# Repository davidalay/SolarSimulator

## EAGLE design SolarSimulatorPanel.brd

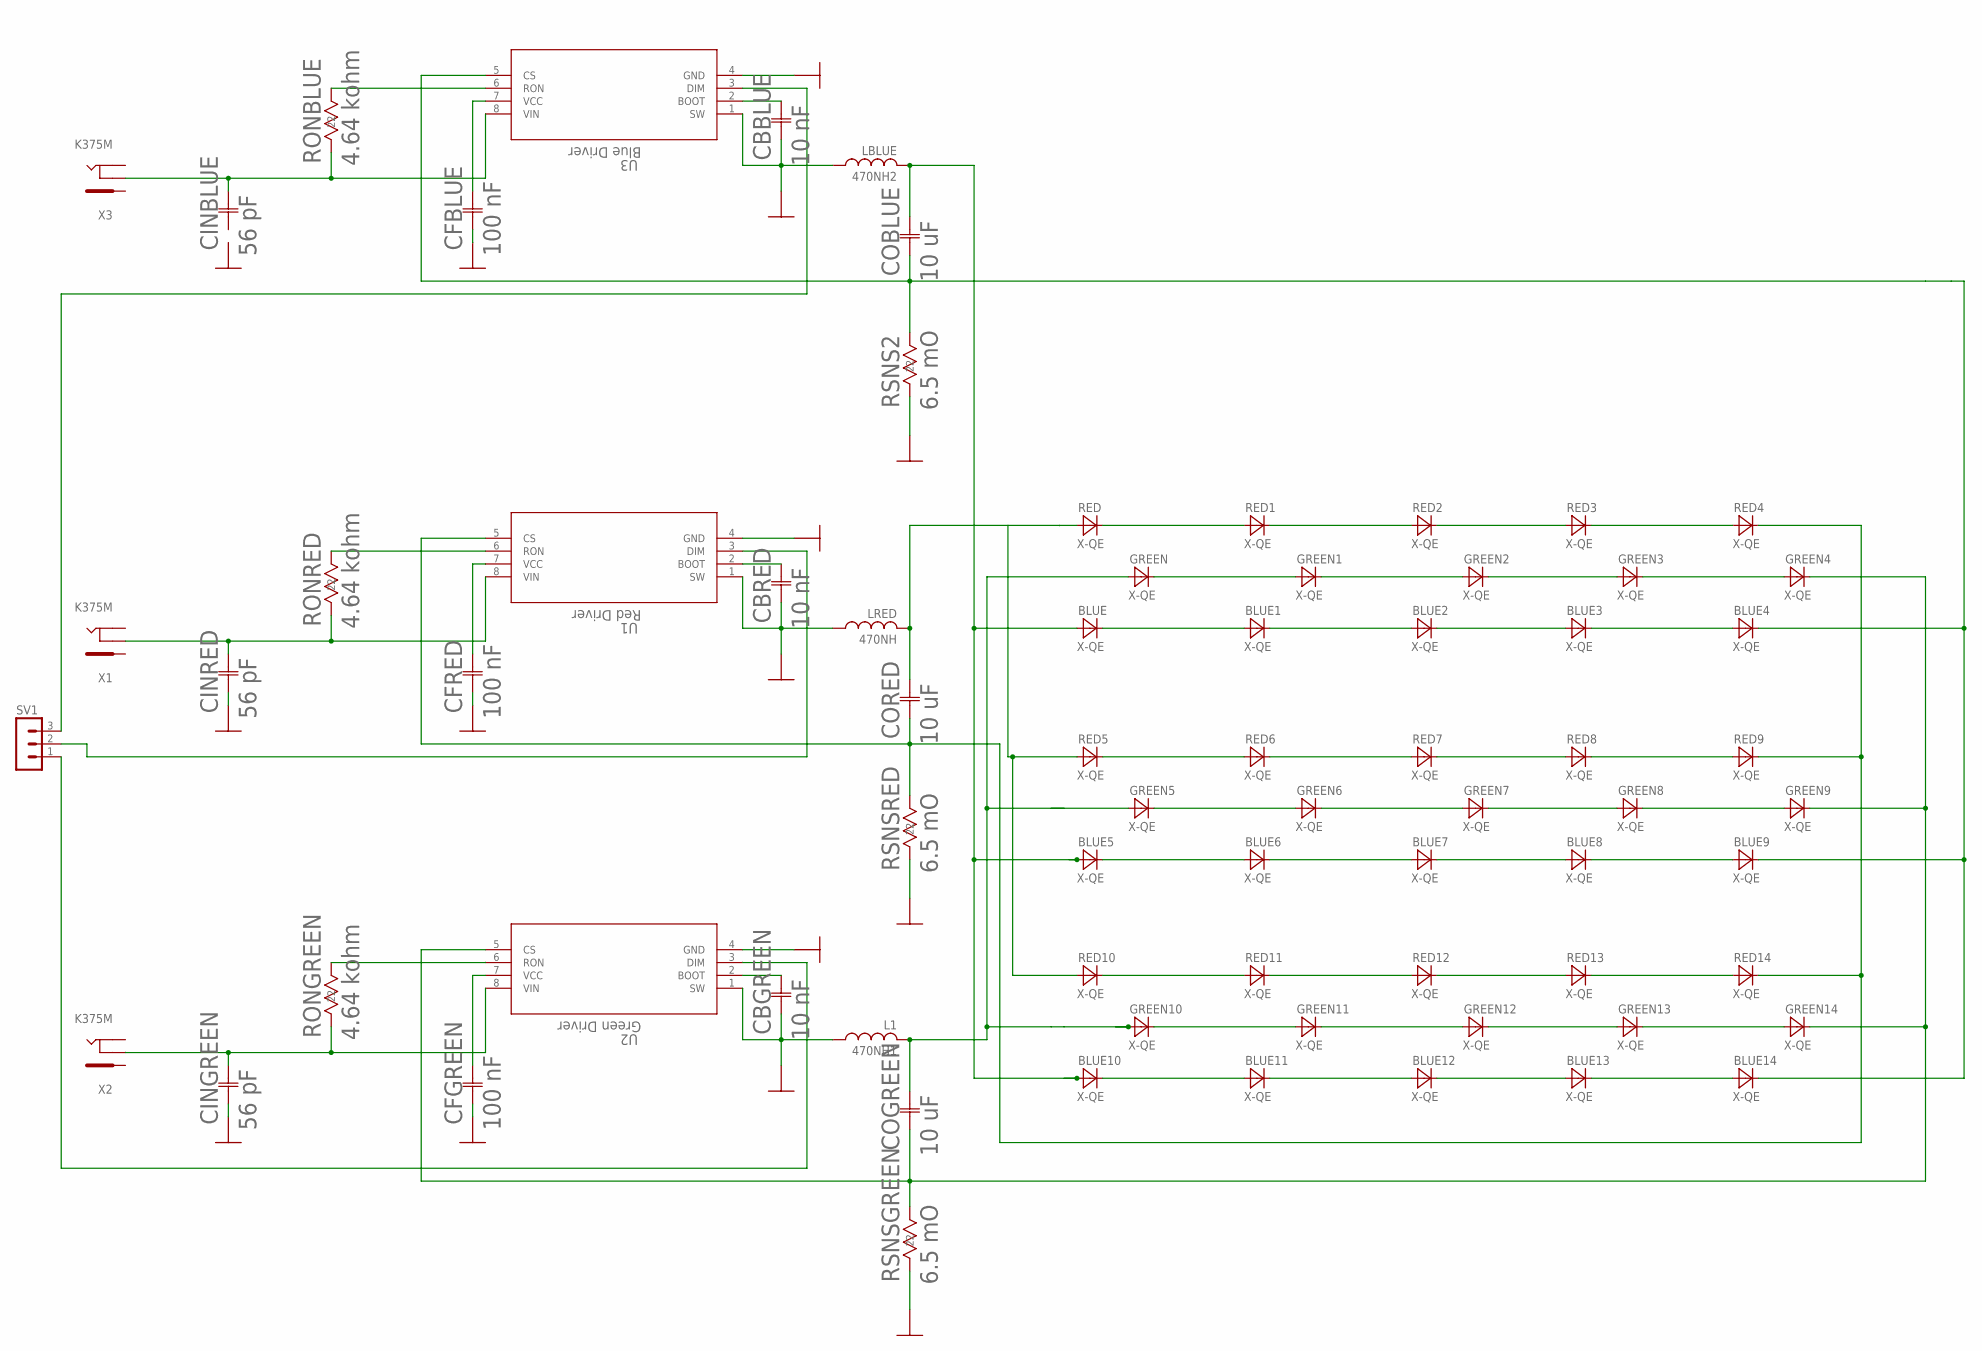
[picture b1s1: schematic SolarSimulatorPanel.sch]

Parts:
470NH: LRED; CAPC2012X135N
470NH1: L1; CAPC2012X135N
470NH2: LBLUE; CAPC2012X135N
BLUE, BLUE1, BLUE2, BLUE3, BLUE4, BLUE5, BLUE6, BLUE7, BLUE8, BLUE9, BLUE10, BLUE11, BLUE12, BLUE13, BLUE14: X-QE
CBBLUE: 10 nF; C1206K
CBGREEN: 10 nF; C1206K
CBRED: 10 nF; C1206K
CFBLUE: 100 nF; C1206
CFGREEN: 100 nF; C1206
CFRED: 100 nF; C1206
CINBLUE: 56 pF; CAP_0603G
CINGREEN: 56 pF; CAP_0603G
CINRED: 56 pF; CAP_0603G
COBLUE: 10 uF; CAP_3225
COGREEN: 10 uF; CAP_3225
CORED: 10 uF; CAP_3225
GREEN, GREEN1, GREEN2, GREEN3, GREEN4, GREEN5, GREEN6, GREEN7, GREEN8, GREEN9, GREEN10, GREEN11, GREEN12, GREEN13, GREEN14: X-QE
RED, RED1, RED2, RED3, RED4, RED5, RED6, RED7, RED8, RED9, RED10, RED11, RED12, RED13, RED14: X-QE
RONBLUE: 4.64 kohm; RC0603N
RONGREEN: 4.64 kohm; RC0603N
RONRED: 4.64 kohm; RC0603N
RSNS2: 6.5 mO; R2512
RSNSGREEN: 6.5 mO; R2512
RSNSRED: 6.5 mO; R2512
SV1: MA03-1
U1: Red Driver; M08A
U2: Green Driver; M08A
U3: Blue Driver; M08A
X1, X2, X3: K375M

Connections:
unnamed: CINRED.2 (22), RONRED.2 (22), U1.8 (VIN), X1.3
unnamed: 470NH.1, CBRED.1 (11), U1.1 (SW)
unnamed: 470NH.2, CORED.2 (22), RED.INPUT (A), RED5.INPUT (A), RED10.INPUT (A)
unnamed: CFRED.2 (22), U1.7 (VCC)
unnamed: RED5.OUTPUT (C), RED6.INPUT (A)
unnamed: RONRED.1 (11), U1.6 (RON)
unnamed: RED6.OUTPUT (C), RED7.INPUT (A)
unnamed: RED7.OUTPUT (C), RED8.INPUT (A)
unnamed: RED8.OUTPUT (C), RED9.INPUT (A)
unnamed: RED10.OUTPUT (C), RED11.INPUT (A)
unnamed: RED11.OUTPUT (C), RED12.INPUT (A)
unnamed: RED12.OUTPUT (C), RED13.INPUT (A)
unnamed: RED13.OUTPUT (C), RED14.INPUT (A)
unnamed: RED.OUTPUT (C), RED1.INPUT (A)
unnamed: RED1.OUTPUT (C), RED2.INPUT (A)
unnamed: RED2.OUTPUT (C), RED3.INPUT (A)
unnamed: RED3.OUTPUT (C), RED4.INPUT (A)
unnamed: 470NH2.1, CBBLUE.1 (11), U3.1 (SW)
unnamed: SV1.2, U1.3 (DIM)
unnamed: CBRED.2 (22), U1.2 (BOOT)
unnamed: 470NH1.1, CBGREEN.1 (11), U2.1 (SW)
unnamed: RONGREEN.1 (11), U2.6 (RON)
unnamed: CINGREEN.2 (22), RONGREEN.2 (22), U2.8 (VIN), X2.3
unnamed: COGREEN.1 (11), GREEN4.OUTPUT (C), GREEN9.OUTPUT (C), GREEN14.OUTPUT (C), RSNSGREEN.1 (11), U2.5 (CS)
unnamed: SV1.1, U2.3 (DIM)
unnamed: CBGREEN.2 (22), U2.2 (BOOT)
unnamed: CFGREEN.2 (22), U2.7 (VCC)
unnamed: GREEN.OUTPUT (C), GREEN1.INPUT (A)
unnamed: GREEN1.OUTPUT (C), GREEN2.INPUT (A)
unnamed: GREEN2.OUTPUT (C), GREEN3.INPUT (A)
unnamed: GREEN3.OUTPUT (C), GREEN4.INPUT (A)
unnamed: GREEN5.OUTPUT (C), GREEN6.INPUT (A)
unnamed: GREEN6.OUTPUT (C), GREEN7.INPUT (A)
unnamed: GREEN7.OUTPUT (C), GREEN8.INPUT (A)
unnamed: GREEN8.OUTPUT (C), GREEN9.INPUT (A)
unnamed: GREEN10.OUTPUT (C), GREEN11.INPUT (A)
unnamed: GREEN11.OUTPUT (C), GREEN12.INPUT (A)
unnamed: GREEN12.OUTPUT (C), GREEN13.INPUT (A)
unnamed: GREEN13.OUTPUT (C), GREEN14.INPUT (A)
unnamed: BLUE.OUTPUT (C), BLUE1.INPUT (A)
unnamed: RONBLUE.1 (11), U3.6 (RON)
unnamed: CINBLUE.2 (22), RONBLUE.2 (22), U3.8 (VIN), X3.3
unnamed: SV1.3, U3.3 (DIM)
unnamed: CBBLUE.2 (22), U3.2 (BOOT)
unnamed: CFBLUE.2 (22), U3.7 (VCC)
unnamed: BLUE1.OUTPUT (C), BLUE2.INPUT (A)
unnamed: BLUE2.OUTPUT (C), BLUE3.INPUT (A)
unnamed: BLUE3.OUTPUT (C), BLUE4.INPUT (A)
unnamed: BLUE5.OUTPUT (C), BLUE6.INPUT (A)
unnamed: BLUE6.OUTPUT (C), BLUE7.INPUT (A)
unnamed: BLUE7.OUTPUT (C), BLUE8.INPUT (A)
unnamed: BLUE8.OUTPUT (C), BLUE9.INPUT (A)
unnamed: BLUE10.OUTPUT (C), BLUE11.INPUT (A)
unnamed: BLUE11.OUTPUT (C), BLUE12.INPUT (A)
unnamed: BLUE12.OUTPUT (C), BLUE13.INPUT (A)
unnamed: BLUE13.OUTPUT (C), BLUE14.INPUT (A)
unnamed: BLUE4.OUTPUT (C), BLUE9.OUTPUT (C), BLUE14.OUTPUT (C), COBLUE.1 (11), RSNS2.1 (11), U3.5 (CS)
unnamed: 470NH2.2, BLUE.INPUT (A), BLUE5.INPUT (A), BLUE10.INPUT (A), COBLUE.2 (22)
unnamed: CORED.1 (11), RED4.OUTPUT (C), RED9.OUTPUT (C), RED14.OUTPUT (C), RSNSRED.1 (11), U1.5 (CS)
unnamed: 470NH1.2, COGREEN.2 (22), GREEN.INPUT (A), GREEN10.INPUT (A)

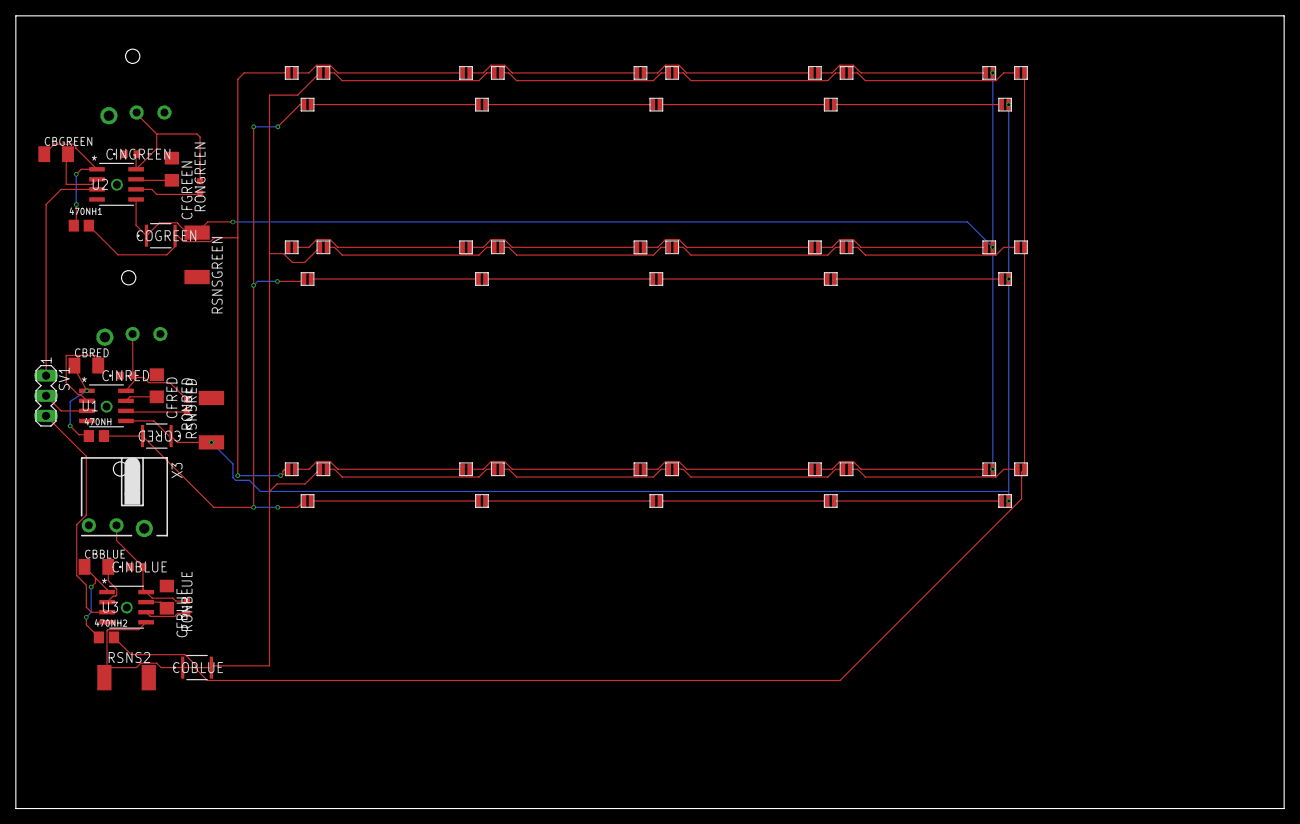
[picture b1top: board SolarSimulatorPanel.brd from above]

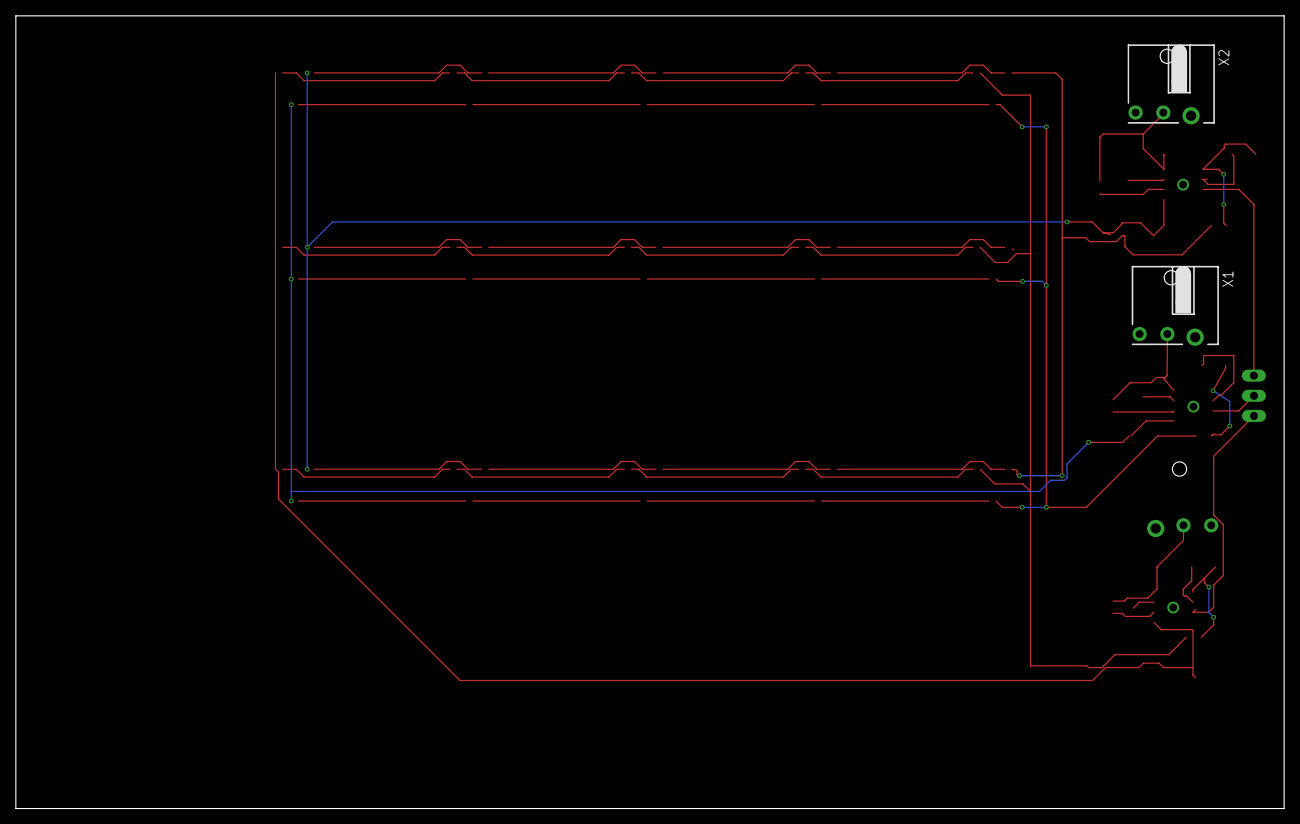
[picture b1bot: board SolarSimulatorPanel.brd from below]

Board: 2 copper layers, 160.0 x 100.0 mm, 73 parts (2 on the bottom side), 60 nets.

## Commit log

2018-09-12 first
